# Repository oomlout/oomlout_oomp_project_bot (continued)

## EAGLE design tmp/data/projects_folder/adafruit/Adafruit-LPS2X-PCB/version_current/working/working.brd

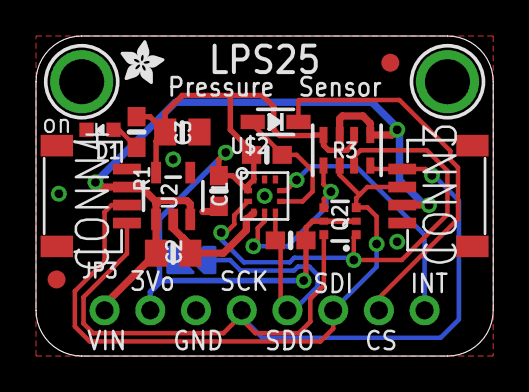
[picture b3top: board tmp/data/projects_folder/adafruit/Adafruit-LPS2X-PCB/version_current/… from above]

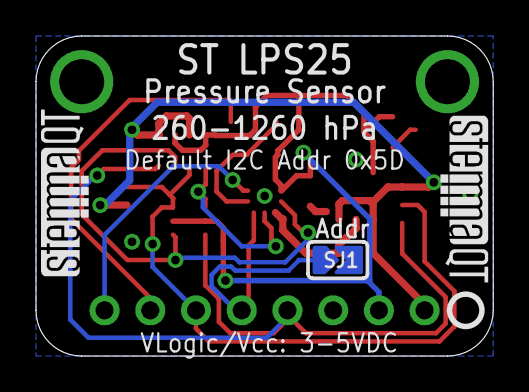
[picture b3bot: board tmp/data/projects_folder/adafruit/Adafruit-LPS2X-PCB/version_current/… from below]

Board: 2 copper layers, 25.4 x 17.8 mm, 24 parts (4 on the bottom side), 12 nets.

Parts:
C1: 0.1uF; 0603-NO
C2, C3: 10uF; 0805-NO
CONN3, CONN4: STEMMA_I2C_QT; JST_SH4
D1: GREEN; CHIPLED_0603_NOOUTLINE
D2: 1N4148; SOD-323
FID3, FID4: FIDUCIAL_1MM
JP3: 1X08_ROUND
Q2: BSS138; SOT363
R1, R4, R5: 10K; 0603-NO
R3: 10K; RESPACK_4X0603
SJ1: SOLDERJUMPER_ARROW_NOPASTE
U2: AP2112K-3.3; SOT23-5
U$1, U$17: MOUNTINGHOLE2.5; MOUNTINGHOLE_2.5_PLATED
U$2: LPS2X_LPS25; HLGA-10L
U$4: ADAFRUIT_2.5MM
U$25: PCBFEAT-REV-040
U$30, U$31: STEMMAQT

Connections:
3.3V: C1.1, C3.1, JP3.2, Q2.2, Q2.5, R1.1, R3.2, R3.4, R4.2, R5.2, U2.5, U$2.1, U$2.10
CS: D2.C, JP3.7
CS_3V: D2.A, R5.1, U$2.6
GND: C1.2, C2.2, C3.2, CONN3.1, CONN4.1, D1.C, JP3.3, SJ1.2, U2.2, U$2.3, U$2.8, U$2.9
INT: JP3.8, U$2.7
unnamed: D1.A, R1.2
SCK/SCL: CONN3.4, CONN4.4, JP3.4, Q2.6, R3.8
SCK_3V: Q2.1, R3.7, U$2.2
SDI/SDA: CONN3.3, CONN4.3, JP3.6, Q2.3, R3.6
SDI_3V: Q2.4, R3.5, U$2.4
SDO/ADR: JP3.5, R4.1, SJ1.1, U$2.5
VCC: C2.1, CONN3.2, CONN4.2, JP3.1, R3.1, R3.3, U2.1, U2.3

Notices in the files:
parts and their libraries:
microbuilder: This work is placed in the public domain, and may be freely used for commercial and non-commercial work with the following conditions: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
